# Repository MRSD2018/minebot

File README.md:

# minebot

http://mrsdprojects.ri.cmu.edu/2017teamb/

Reducing Cost, Risk, and Error in Landmine Detection

Landmines are a tragic remnant of war that the threaten economic security, mobility, and lives of people around the world. Though there has been a plethora of research in landmine sensing in the last few decades, most methods are expensive, energy-intensive, and result in a high number of false positives. ClearField Robotics aims to improve outcomes in the field by reducing the time and cost of land surveying.

By incorporating multi-modal sensing systems, we can reduce the need for singular, highly sensitive, and expensive equipment with sensor fusion. The goal of ClearField Robotics is to develop a low cost, user-friendly, and adoptable method of landmine detection without sacrificing accuracy. We combine a traditional metal detector (for broad sweeping) and an automated probing mechanism (to classify the shape of any detected metal objects) to reduce the number of false positives, increase demining speed and reduce demining costs.

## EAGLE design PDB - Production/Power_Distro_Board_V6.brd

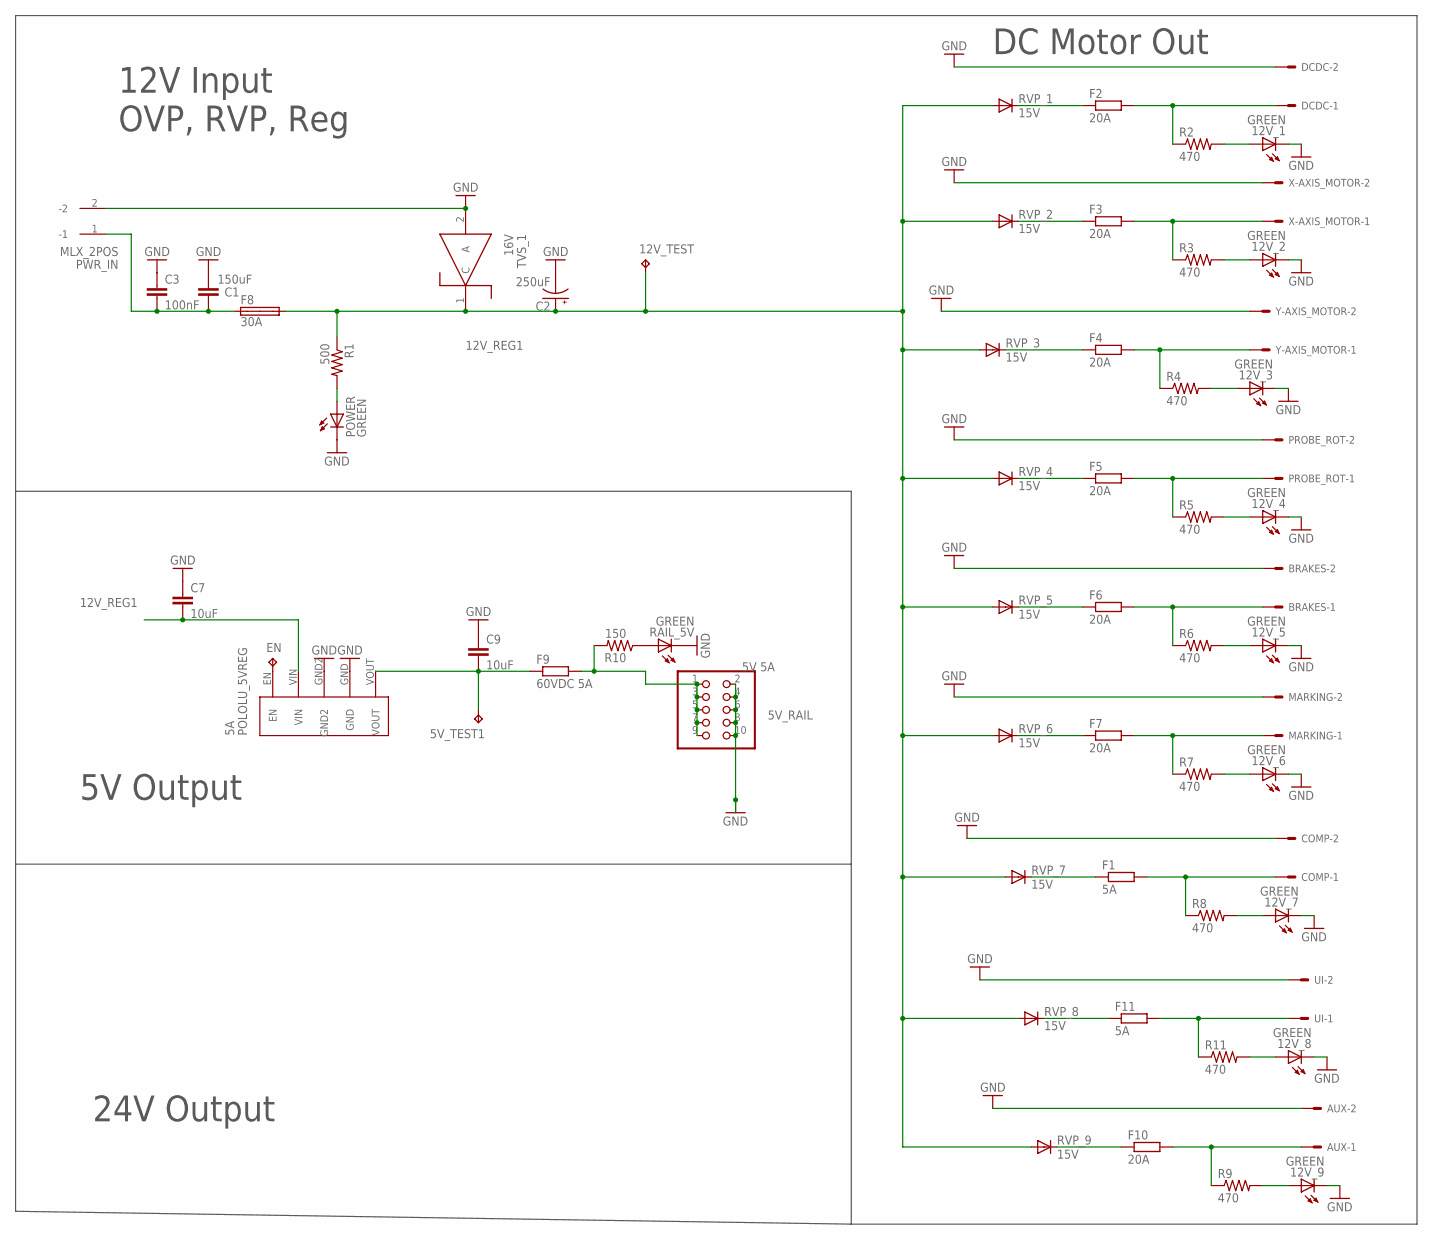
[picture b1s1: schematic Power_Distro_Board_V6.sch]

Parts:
5A: POLOLU_5VREG; SIP5
5V_RAIL: 5V 5A; 2X05
5V_TEST1, 12V_TEST: TPPAD1-13; P1-13
12V_1, 12V_2, 12V_3, 12V_4, 12V_5, 12V_6, 12V_7, 12V_8, 12V_9: GREEN; SML1206
AUX: 555X-2V; 5566-2
BRAKES: 555X-2V; 5566-2
C1: 150uF; C1210
C2: 250uF; CPOL-RADIAL-5MM-10MM
C3: 100nF; C1210
C7, C9: 10uF; C1210
COMP: 555X-2V; 5566-2
DCDC: 555X-2V; 5566-2
EN: TPPAD1-13; P1-13
F1, F11: 5A; M1206
F2, F3, F4, F5, F6, F7, F10: 20A; M1206
F8: 30A; SHK20L
F9: 60VDC 5A; M1206
MARKING: 555X-2V; 5566-2
POWER: GREEN; SML1206
PROBE_ROT: 555X-2V; 5566-2
PWR_IN: MLX_2POS; .084MLX
R1: 500; R1206
R2, R3, R4, R5, R6, R7, R8, R9, R11: 470; R1206
R10: 150; R1206
RAIL_5V: GREEN; SML1206
RVP_1, RVP_2, RVP_3, RVP_4, RVP_5, RVP_6, RVP_7, RVP_8, RVP_9: 15V; TO220ACS
TVS_1: 16V; DO-214AC
UI: 555X-2V; 5566-2
X-AXIS_MOTOR: 555X-2V; 5566-2
Y-AXIS_MOTOR: 555X-2V; 5566-2

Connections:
5V_REG3: 5V_RAIL.1, 5V_RAIL.3, 5V_RAIL.5, 5V_RAIL.7, 5V_RAIL.9, F9.2, R10.2
12V_REG1: 5A.VIN, 12V_TEST.TP, C2.+, C7.2, F8.2A, R1.1, RVP_1.A, RVP_2.A, RVP_3.A, RVP_4.A, RVP_5.A, RVP_6.A, RVP_7.A, RVP_8.A, RVP_9.A, TVS_1.1 (C)
GND: 5A.GND, 5A.GND2, 5V_RAIL.2, 5V_RAIL.4, 5V_RAIL.6, 5V_RAIL.8, 5V_RAIL.10, 12V_1.C, 12V_2.C, 12V_3.C, 12V_4.C, 12V_5.C, 12V_6.C, 12V_7.C, 12V_8.C, 12V_9.C, AUX.2, BRAKES.2, C1.2, C2.-, C3.1, C7.1, C9.1, COMP.2, DCDC.2, MARKING.2, POWER.C, PROBE_ROT.2, PWR_IN.2 (-2), RAIL_5V.C, TVS_1.2 (A), UI.2, X-AXIS_MOTOR.2, Y-AXIS_MOTOR.2
unnamed: POWER.A, R1.2
unnamed: C1.1, C3.2, F8.1A, PWR_IN.1 (-1)
unnamed: F1.1, RVP_7.C
unnamed: F2.1, RVP_1.C
unnamed: F6.1, RVP_5.C
unnamed: 5A.EN, EN.TP
unnamed: 12V_1.A, R2.2
unnamed: F10.1, RVP_9.C
unnamed: R10.1, RAIL_5V.A
unnamed: DCDC.1, F2.2, R2.1
unnamed: 12V_5.A, R6.2
unnamed: F3.1, RVP_2.C
unnamed: 12V_9.A, R9.2
unnamed: 12V_2.A, R3.2
unnamed: BRAKES.1, F6.2, R6.1
unnamed: F3.2, R3.1, X-AXIS_MOTOR.1
unnamed: F7.1, RVP_6.C
unnamed: 12V_6.A, R7.2
unnamed: F4.1, RVP_3.C
unnamed: F7.2, MARKING.1, R7.1
unnamed: 12V_3.A, R4.2
unnamed: F4.2, R4.1, Y-AXIS_MOTOR.1
unnamed: F5.1, RVP_4.C
unnamed: 12V_4.A, R5.2
unnamed: F5.2, PROBE_ROT.1, R5.1
unnamed: 12V_7.A, R8.2
unnamed: COMP.1, F1.2, R8.1
unnamed: F11.1, RVP_8.C
unnamed: 5A.VOUT, 5V_TEST1.TP, C9.2, F9.1
unnamed: 12V_8.A, R11.2
unnamed: F11.2, R11.1, UI.1
unnamed: AUX.1, F10.2, R9.1

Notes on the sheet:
12V Input OVP, RVP, Reg
DC Motor Out
5V Output
24V Output

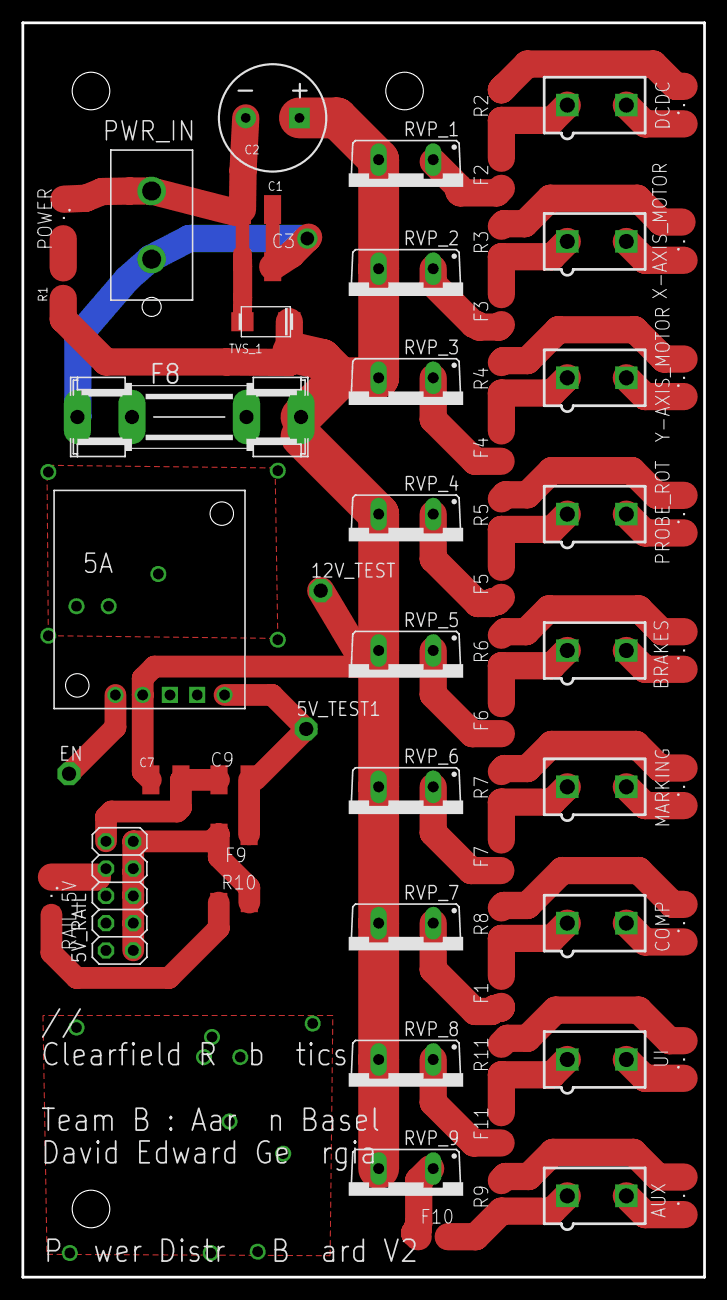
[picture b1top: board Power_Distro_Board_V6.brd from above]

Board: 2 copper layers, 63.5 x 116.8 mm, 63 parts (0 on the bottom side), 35 nets.

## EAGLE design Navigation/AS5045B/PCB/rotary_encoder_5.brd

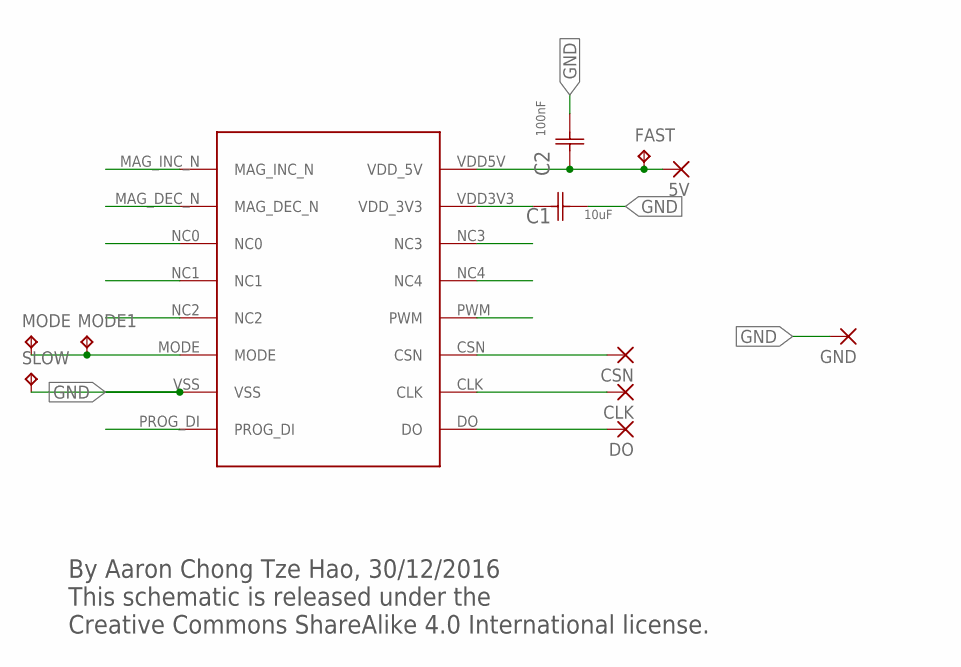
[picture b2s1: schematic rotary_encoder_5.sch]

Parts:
5V: 1,6/0,8
C1: 10uF; CAP_0805_100NF
C2: 100nF; CAP_0805_100NF
CLK: 1,6/0,8
CSN: 1,6/0,8
DO: 1,6/0,8
FAST: TPTP10SQ; TP10SQ
GND: 1,6/0,8
MODE, MODE1: TPTP10SQ; TP10SQ
SLOW: TPTP10SQ; TP10SQ
U$1: AS5045_ROTARY_ENCODER

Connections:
5V: 5V.1, C2.1 (C1), FAST.TP, U$1.VDD5V (VDD_5V)
CLK: CLK.1, U$1.CLK
CSN: CSN.1, U$1.CSN
DO: DO.1, U$1.DO
GND: C1.2 (C2), C2.2 (C2), GND.1, SLOW.TP, U$1.VSS
unnamed: MODE.TP, MODE1.TP, U$1.MODE
unnamed: C1.1 (C1), U$1.VDD3V3 (VDD_3V3)

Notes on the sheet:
By Aaron Chong Tze Hao, 30/12/2016 This schematic is released under the Creative Commons ShareAlike 4.0 International license.

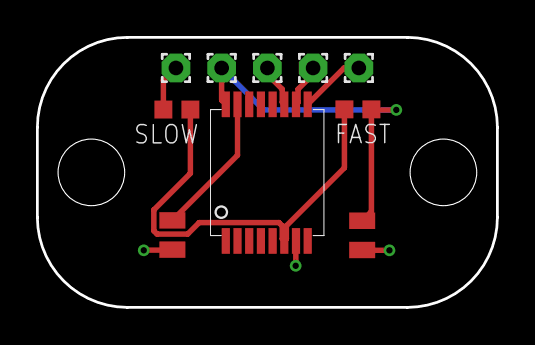
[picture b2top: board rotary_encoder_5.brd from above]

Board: 2 copper layers, 25.6 x 15.0 mm, 12 parts (0 on the bottom side), 7 nets.

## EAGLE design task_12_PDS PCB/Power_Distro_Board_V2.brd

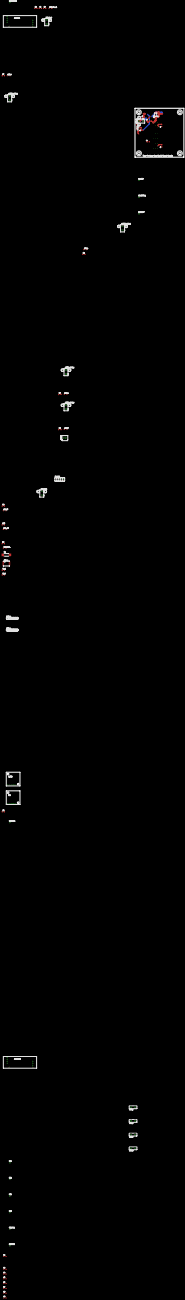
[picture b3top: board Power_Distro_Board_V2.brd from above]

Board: 2 copper layers, 63.5 x 63.6 mm, 70 parts (0 on the bottom side), 48 nets.

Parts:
2.5A, 5A: POLOLU_5VREG; SIP5
5V_RAIL: 5V 5A; 2X05
5V_TEST, 5V_TEST1, 12V_TEST, 24V_TEST_1, 24V_TEST_2: TPPAD1-13; P1-13
12V_1, 12V_2, 12V_3, 12V_4, 24V_2A_1_, 24V_2A_1_1: GREEN; SML1206
24V_2A_1, 24V_2A_2: 5566-2
24V_REG, 24V_REG1: POLOLU_24VSTEPUP; 2X4PIN_REG
C1: 150uF; C1206
C1_1: 100nF; C1206
C1_2, C3, C4, C5, C6, C7, C8, C9: 10uF; C1206
C2: 100uF; C1206
EN1, EN2: TPPAD1-13; P1-13
ENABLE1, ENABLE2: TPPAD1-13; P1-13
ENC_1: ENCODER_AS5045B; SSOP16
F1: 60VDC 50A; NANO
F2, F3, F4, F5: 60VDC 20A; R1206W
F6, F7, F8: 60VDC 3A; R1206W
F9: 60VDC 5A; R1206W
MAIN_1: 1X06
MOTOR_OUT_1, MOTOR_OUT_2, MOTOR_OUT_3, MOTOR_OUT_4: 5566-2
PG1, PG2: TPPAD1-13; P1-13
POWER: GREEN; SML1206
PWR_IN: 5566-2
R1: 500; R1206
R2, R3, R4, R7: 470; R1206
R5, R6: 1100; R1206
R9, R10: 150; R1206
RAIL_5V: GREEN; SML1206
RPI_5V: GREEN; SML1206
RPI_OUT: C-GRID-02-70543; 70543-02
RVP_1, RVP_2, RVP_3, RVP_4: 15V; TO220ACS
SUB_1: 1X06
TVS_1: 16V; DO-214AC

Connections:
5V_REG: 2.5A.VOUT, 5V_TEST.TP, C8.2, F8.1
5V_REG1: F8.2, R9.2, RPI_OUT.1
5V_REG3: 5V_RAIL.1, 5V_RAIL.3, 5V_RAIL.5, 5V_RAIL.7, 5V_RAIL.9, F9.2, R10.2
12V_REG: 12V_TEST.TP, C2.2, F1.VIN-, R1.1, RVP_1.A, RVP_2.A, RVP_3.A, RVP_4.A, TVS_1.1
12V_REG_TVS: 2.5A.VIN, 5A.VIN, 24V_REG.VIN1, 24V_REG.VIN2, 24V_REG1.VIN1, 24V_REG1.VIN2, C3.2, C5.2, C7.2
A_1: ENC_1.3, SUB_1.3
B_1: ENC_1.4, SUB_1.4
CLK_1: ENC_1.10, MAIN_1.4
CSN_1: ENC_1.11, MAIN_1.3
DO_1: ENC_1.9, MAIN_1.5
GND: 2.5A.GND, 5A.GND, 5V_RAIL.2, 5V_RAIL.4, 5V_RAIL.6, 5V_RAIL.8, 5V_RAIL.10, 12V_1.C, 12V_2.C, 12V_3.C, 12V_4.C, 24V_2A_1.2, 24V_2A_1_.C, 24V_2A_1_1.C, 24V_2A_2.2, 24V_REG.GND1, 24V_REG.GND2, 24V_REG.GND3, 24V_REG.GND4, 24V_REG1.GND1, 24V_REG1.GND2, 24V_REG1.GND3, 24V_REG1.GND4, C1.1, C2.1, C3.1, C4.1, C5.1, C6.1, C7.1, C8.1, C9.1, MOTOR_OUT_1.2, MOTOR_OUT_2.2, MOTOR_OUT_3.2, MOTOR_OUT_4.2, POWER.C, PWR_IN.2, RAIL_5V.C, RPI_5V.C, RPI_OUT.2, TVS_1.2
GND_1: C1_1.2, C1_2.2, ENC_1.7, MAIN_1.2
I_1: ENC_1.6, SUB_1.5
MAG_DEC_N_1: ENC_1.2, SUB_1.2
MAG_INC_N_1: ENC_1.1, SUB_1.1
unnamed: POWER.A, R1.2
unnamed: 2.5A.PG, PG1.TP
unnamed: C1.2, F1.VIN+, PWR_IN.1
unnamed: C1_2.1, ENC_1.15
unnamed: F2.1, RVP_1.C
unnamed: 2.5A.EN, EN1.TP
unnamed: 24V_REG1.VOUT1, 24V_REG1.VOUT2, 24V_TEST_1.TP, C4.2
unnamed: 5A.PG, PG2.TP
unnamed: 12V_1.A, R2.2
unnamed: R9.1, RPI_5V.A
unnamed: R10.1, RAIL_5V.A
unnamed: F2.2, MOTOR_OUT_1.1, R2.1
unnamed: F3.1, RVP_2.C
unnamed: 5A.EN, EN2.TP
unnamed: 12V_2.A, R3.2
unnamed: 24V_2A_1_1.A, R6.2
unnamed: F3.2, MOTOR_OUT_2.1, R3.1
unnamed: 24V_2A_1.1, F6.2, R5.1
unnamed: F4.1, RVP_3.C
unnamed: 12V_3.A, R4.2
unnamed: F4.2, MOTOR_OUT_3.1, R4.1
unnamed: F5.1, RVP_4.C
unnamed: 12V_4.A, R7.2
unnamed: F5.2, MOTOR_OUT_4.1, R7.1
unnamed: 24V_2A_1_.A, R5.2
unnamed: 24V_REG1.ENABLE, ENABLE1.TP
unnamed: 24V_REG.VOUT1, 24V_REG.VOUT2, 24V_TEST_2.TP, C6.2
unnamed: 5A.VOUT, 5V_TEST1.TP, C9.2, F9.1
unnamed: 24V_2A_2.1, F7.2, R6.1
unnamed: 24V_REG.ENABLE, ENABLE2.TP
PDIO_1: ENC_1.8, SUB_1.6
PWM_1: ENC_1.12, MAIN_1.6
VIN_1: C1_1.1, ENC_1.16, MAIN_1.1

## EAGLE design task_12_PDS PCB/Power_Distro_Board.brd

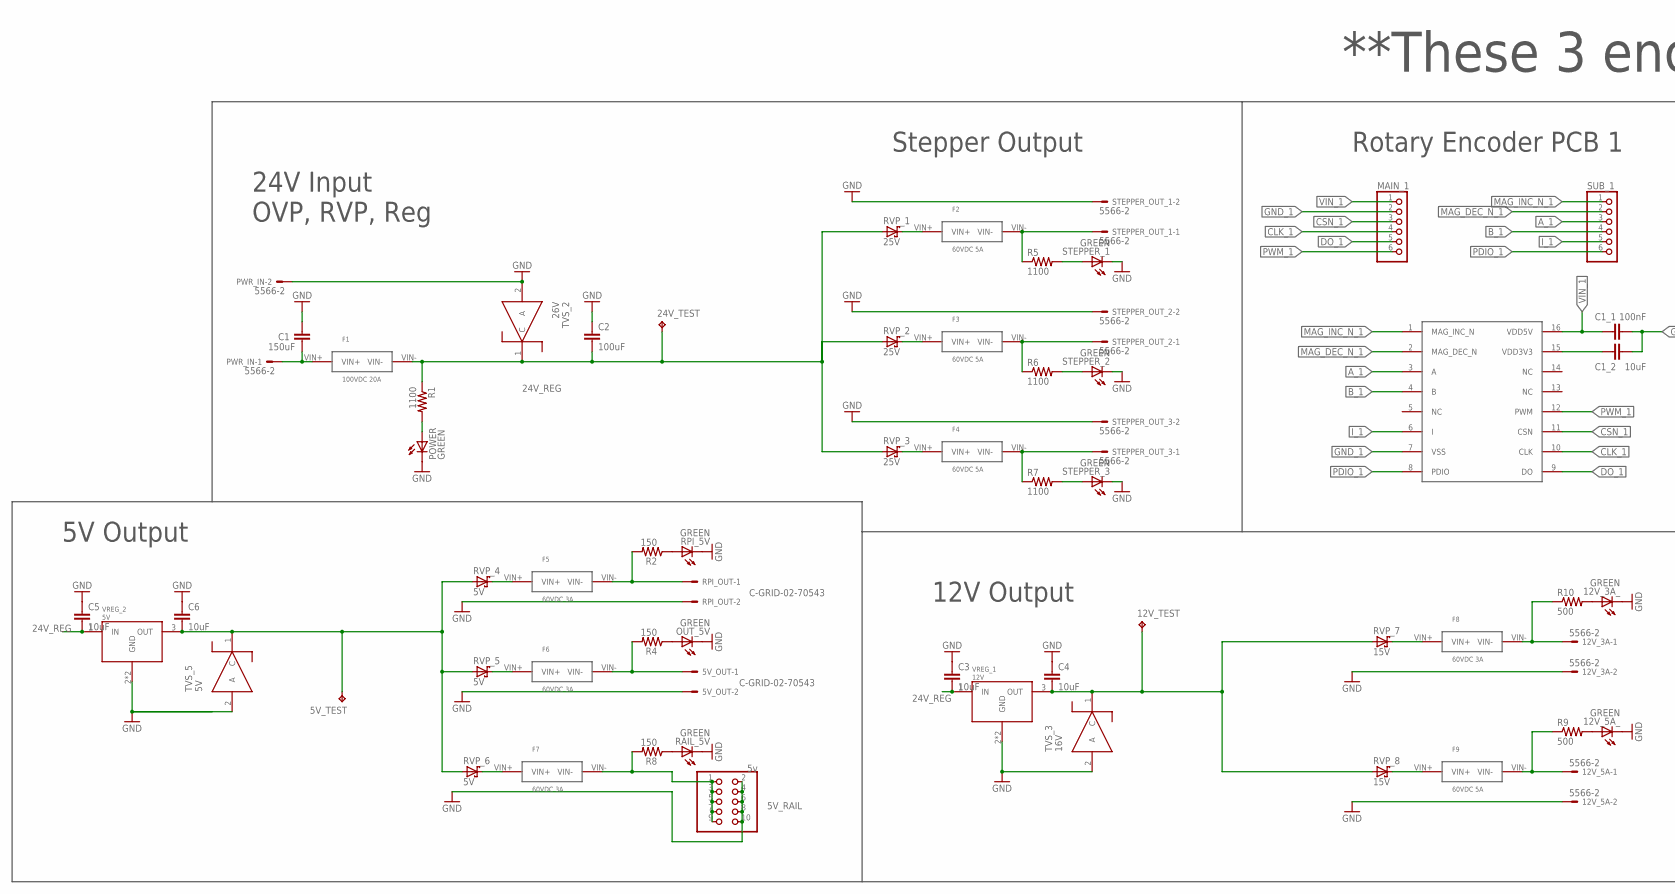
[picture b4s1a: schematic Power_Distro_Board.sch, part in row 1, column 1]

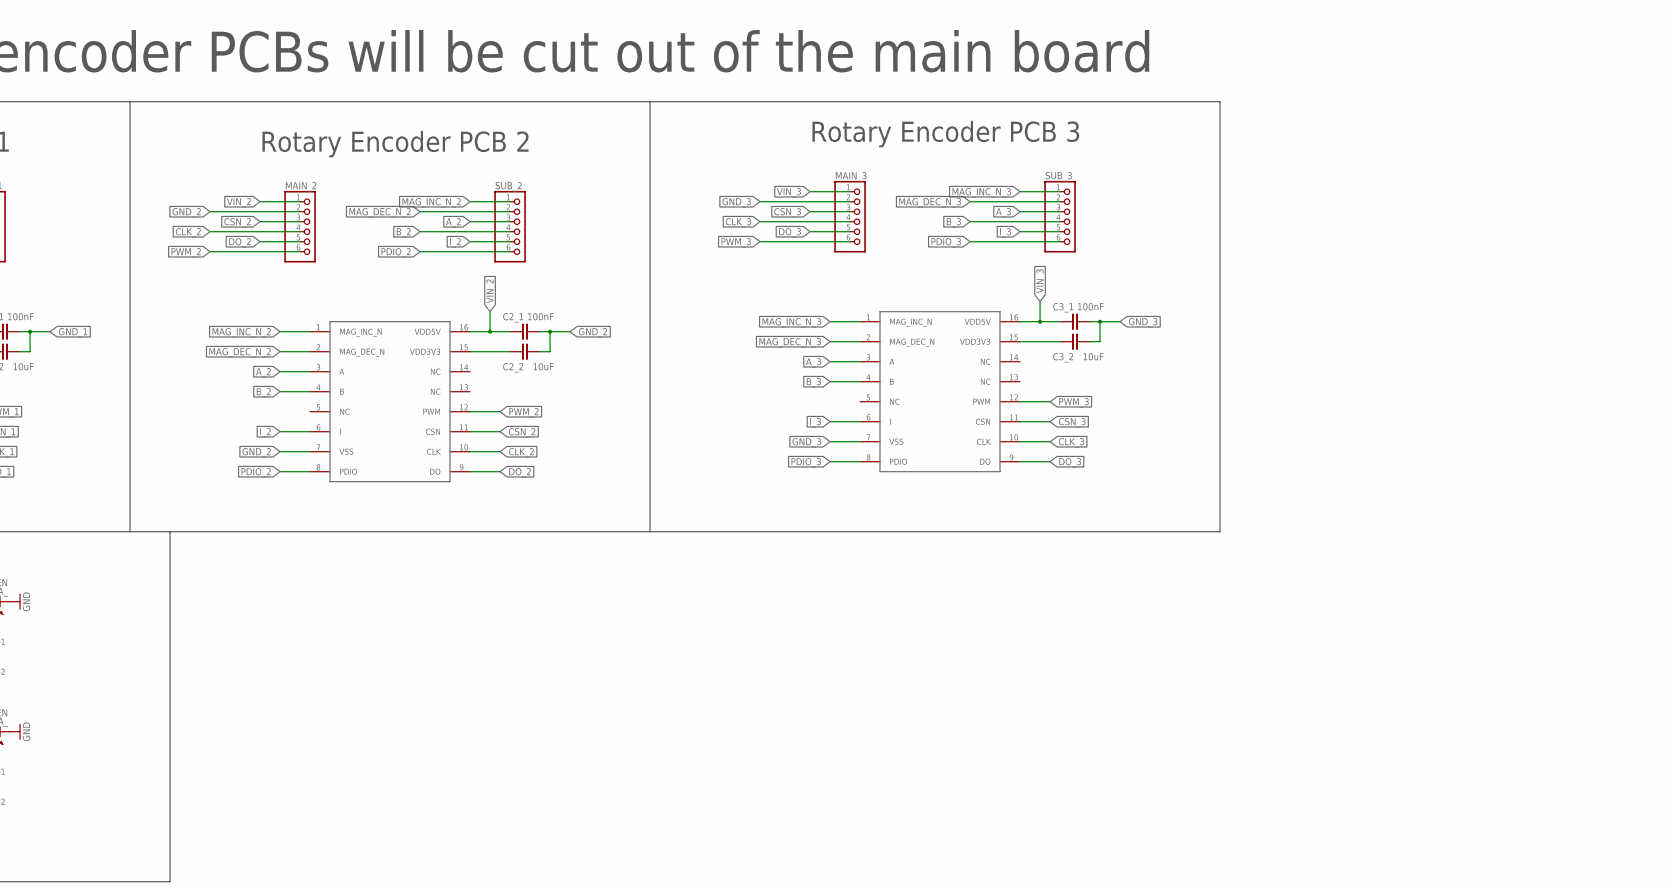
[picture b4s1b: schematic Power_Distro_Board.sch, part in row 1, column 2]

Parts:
5V_OUT: C-GRID-02-70543; 70543-02
5V_RAIL: 5v; 2X05
5V_TEST, 12V_TEST, 24V_TEST: TPPAD1-13; P1-13
12V_3A, 12V_5A: 5566-2
12V_3A_, 12V_5A_: GREEN; SML1206
C1: 150uF; C1206
C1_1, C2_1, C3_1: 100nF; C1206
C1_2, C2_2, C3, C3_2, C4, C5, C6: 10uF; C1206
C2: 100uF; C1206
ENC_1, ENC_2, ENC_3: ENCODER_AS5045B; SSOP16
F1: 100VDC 20A; NANO
F2, F3, F4, F9: 60VDC 5A; OMNI_BLOCK
F5, F6, F7, F8: 60VDC 3A; OMNI_BLOCK
MAIN_1, MAIN_2, MAIN_3: PINHD-1X6; 1X06
OUT_5V: GREEN; SML1206
POWER: GREEN; SML1206
PWR_IN: 5566-2
R1, R5, R6, R7: 1100; R1206
R2, R4, R8: 150; R1206
R9, R10: 500; R1206
RAIL_5V: GREEN; SML1206
RPI_5V: GREEN; SML1206
RPI_OUT: C-GRID-02-70543; 70543-02
RVP_1, RVP_2, RVP_3: 25V; SMC
RVP_4, RVP_5, RVP_6: 5V; SMC
RVP_7, RVP_8: 15V; SMC
STEPPER_1, STEPPER_2, STEPPER_3: GREEN; SML1206
STEPPER_OUT_1, STEPPER_OUT_2, STEPPER_OUT_3: 5566-2
SUB_1, SUB_2, SUB_3: PINHD-1X6; 1X06
TVS_2: 26V; DO-214AC
TVS_3: 16V; DO-214AC
TVS_5: 5V; DO-214AC
VREG_1: 12V; TO-263-3
VREG_2: 5V; TO-263-3

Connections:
5V_REG: 5V_TEST.TP, C6.2, RVP_4.A, RVP_5.A, RVP_6.A, TVS_5.1 (C), VREG_2.3 (OUT)
5V_REG1: F5.VIN-, R2.2, RPI_OUT.1
5V_REG2: 5V_OUT.1, F6.VIN-, R4.2
5V_REG3: 5V_RAIL.1, 5V_RAIL.3, 5V_RAIL.5, 5V_RAIL.7, 5V_RAIL.9, F7.VIN-, R8.2
12V_REG: 12V_TEST.TP, C4.2, RVP_7.A, RVP_8.A, TVS_3.1 (C), VREG_1.3 (OUT)
12V_REG1: 12V_5A.1, F9.VIN-, R9.1
12V_REG2: 12V_3A.1, F8.VIN-, R10.1
24V_REG: 24V_TEST.TP, C2.2, C3.2, C5.2, F1.VIN-, R1.1, RVP_1.A, RVP_2.A, RVP_3.A, TVS_2.1 (C), VREG_1.1 (IN), VREG_2.1 (IN)
A_1: ENC_1.3 (A), SUB_1.3
A_2: ENC_2.3 (A), SUB_2.3
A_3: ENC_3.3 (A), SUB_3.3
B_1: ENC_1.4 (B), SUB_1.4
B_2: ENC_2.4 (B), SUB_2.4
B_3: ENC_3.4 (B), SUB_3.4
CLK_1: ENC_1.10 (CLK), MAIN_1.4
CLK_2: ENC_2.10 (CLK), MAIN_2.4
CLK_3: ENC_3.10 (CLK), MAIN_3.4
CSN_1: ENC_1.11 (CSN), MAIN_1.3
CSN_2: ENC_2.11 (CSN), MAIN_2.3
CSN_3: ENC_3.11 (CSN), MAIN_3.3
DO_1: ENC_1.9 (DO), MAIN_1.5
DO_2: ENC_2.9 (DO), MAIN_2.5
DO_3: ENC_3.9 (DO), MAIN_3.5
GND: 5V_OUT.2, 5V_RAIL.2, 5V_RAIL.4, 5V_RAIL.6, 5V_RAIL.8, 5V_RAIL.10, 12V_3A.2, 12V_3A_.C, 12V_5A.2, 12V_5A_.C, C1.1, C2.1, C3.1, C4.1, C5.1, C6.1, OUT_5V.C, POWER.C, PWR_IN.2, RAIL_5V.C, RPI_5V.C, RPI_OUT.2, STEPPER_1.C, STEPPER_2.C, STEPPER_3.C, STEPPER_OUT_1.2, STEPPER_OUT_2.2, STEPPER_OUT_3.2, TVS_2.2 (A), TVS_3.2 (A), TVS_5.2 (A), VREG_1.2 (GND), VREG_1.4 (GND), VREG_2.2 (GND), VREG_2.4 (GND)
GND_1: C1_1.2, C1_2.2, ENC_1.7 (VSS), MAIN_1.2
GND_2: C2_1.2, C2_2.2, ENC_2.7 (VSS), MAIN_2.2
GND_3: C3_1.2, C3_2.2, ENC_3.7 (VSS), MAIN_3.2
I_1: ENC_1.6 (I), SUB_1.5
I_2: ENC_2.6 (I), SUB_2.5
I_3: ENC_3.6 (I), SUB_3.5
MAG_DEC_N_1: ENC_1.2 (MAG_DEC_N), SUB_1.2
MAG_DEC_N_2: ENC_2.2 (MAG_DEC_N), SUB_2.2
MAG_DEC_N_3: ENC_3.2 (MAG_DEC_N), SUB_3.2
MAG_INC_N_1: ENC_1.1 (MAG_INC_N), SUB_1.1
MAG_INC_N_2: ENC_2.1 (MAG_INC_N), SUB_2.1
MAG_INC_N_3: ENC_3.1 (MAG_INC_N), SUB_3.1
unnamed: POWER.A, R1.2
unnamed: C2_2.1, ENC_2.15 (VDD3V3)
unnamed: C1.2, F1.VIN+, PWR_IN.1
unnamed: C1_2.1, ENC_1.15 (VDD3V3)
unnamed: F2.VIN+, RVP_1.C
unnamed: C3_2.1, ENC_3.15 (VDD3V3)
unnamed: F5.VIN+, RVP_4.C
unnamed: R5.2, STEPPER_1.A
unnamed: R2.1, RPI_5V.A
unnamed: R8.1, RAIL_5V.A
unnamed: F2.VIN-, R5.1, STEPPER_OUT_1.1
unnamed: F3.VIN+, RVP_2.C
unnamed: R6.2, STEPPER_2.A
unnamed: 12V_5A_.A, R9.2
unnamed: F3.VIN-, R6.1, STEPPER_OUT_2.1
unnamed: OUT_5V.A, R4.1
unnamed: F4.VIN+, RVP_3.C
unnamed: R7.2, STEPPER_3.A
unnamed: F4.VIN-, R7.1, STEPPER_OUT_3.1
unnamed: F6.VIN+, RVP_5.C
unnamed: 12V_3A_.A, R10.2
unnamed: F7.VIN+, RVP_6.C
unnamed: F8.VIN+, RVP_7.C
unnamed: F9.VIN+, RVP_8.C
PDIO_1: ENC_1.8 (PDIO), SUB_1.6
PDIO_2: ENC_2.8 (PDIO), SUB_2.6
PDIO_3: ENC_3.8 (PDIO), SUB_3.6
PWM_1: ENC_1.12 (PWM), MAIN_1.6
PWM_2: ENC_2.12 (PWM), MAIN_2.6
PWM_3: ENC_3.12 (PWM), MAIN_3.6
VIN_1: C1_1.1, ENC_1.16 (VDD5V), MAIN_1.1
VIN_2: C2_1.1, ENC_2.16 (VDD5V), MAIN_2.1
VIN_3: C3_1.1, ENC_3.16 (VDD5V), MAIN_3.1

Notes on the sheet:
24V Input OVP, RVP, Reg
Stepper Output
5V Output
12V Output
Rotary Encoder PCB 1
Rotary Encoder PCB 2
Rotary Encoder PCB 3
**These 3 encoder PCBs will be cut out of the main board

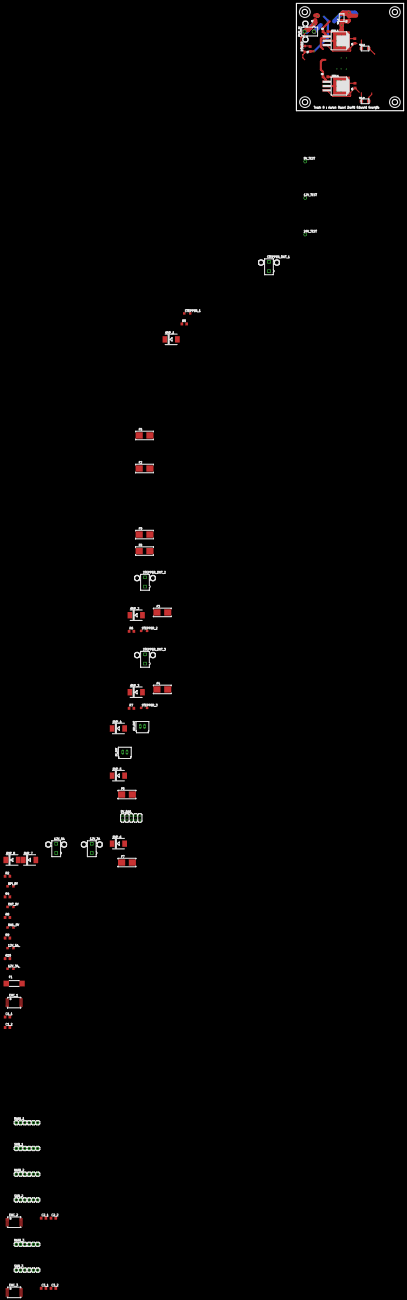
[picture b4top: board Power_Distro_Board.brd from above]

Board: 2 copper layers, 63.5 x 63.6 mm, 73 parts (0 on the bottom side), 69 nets.

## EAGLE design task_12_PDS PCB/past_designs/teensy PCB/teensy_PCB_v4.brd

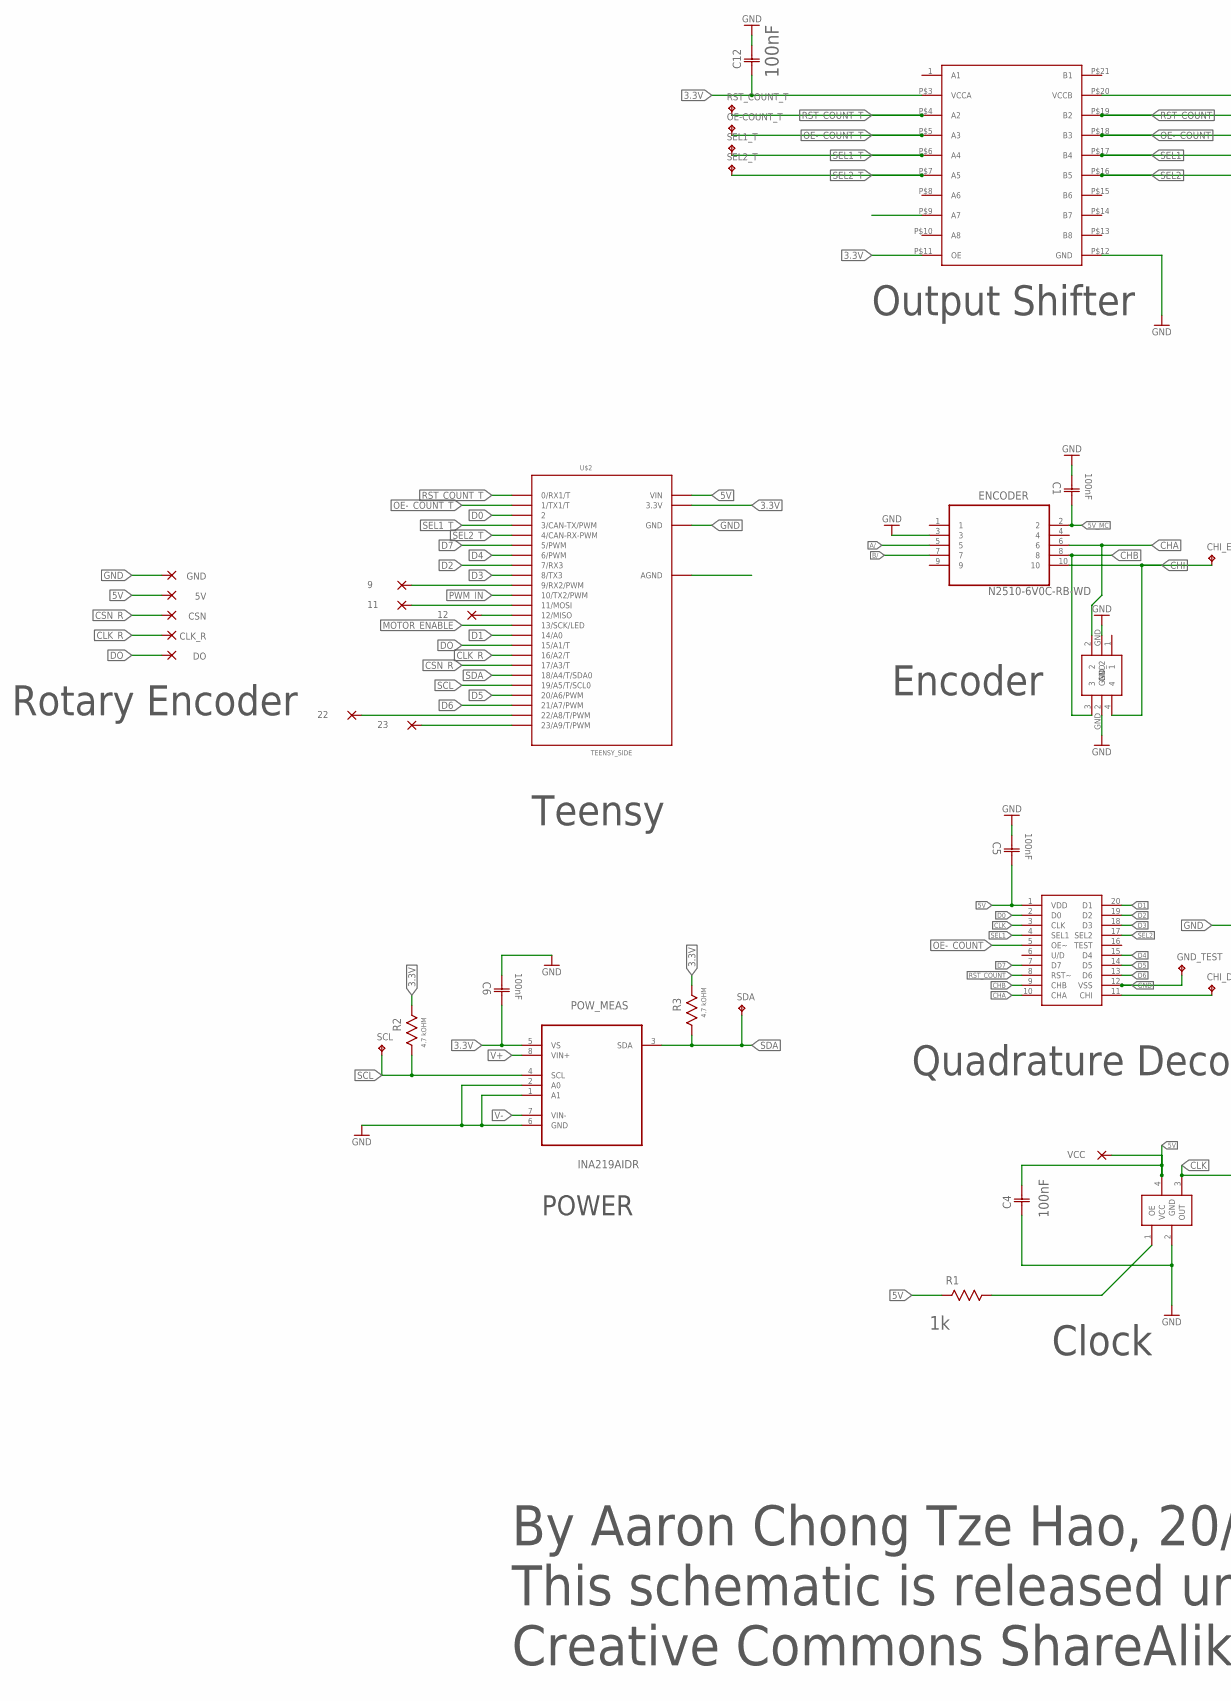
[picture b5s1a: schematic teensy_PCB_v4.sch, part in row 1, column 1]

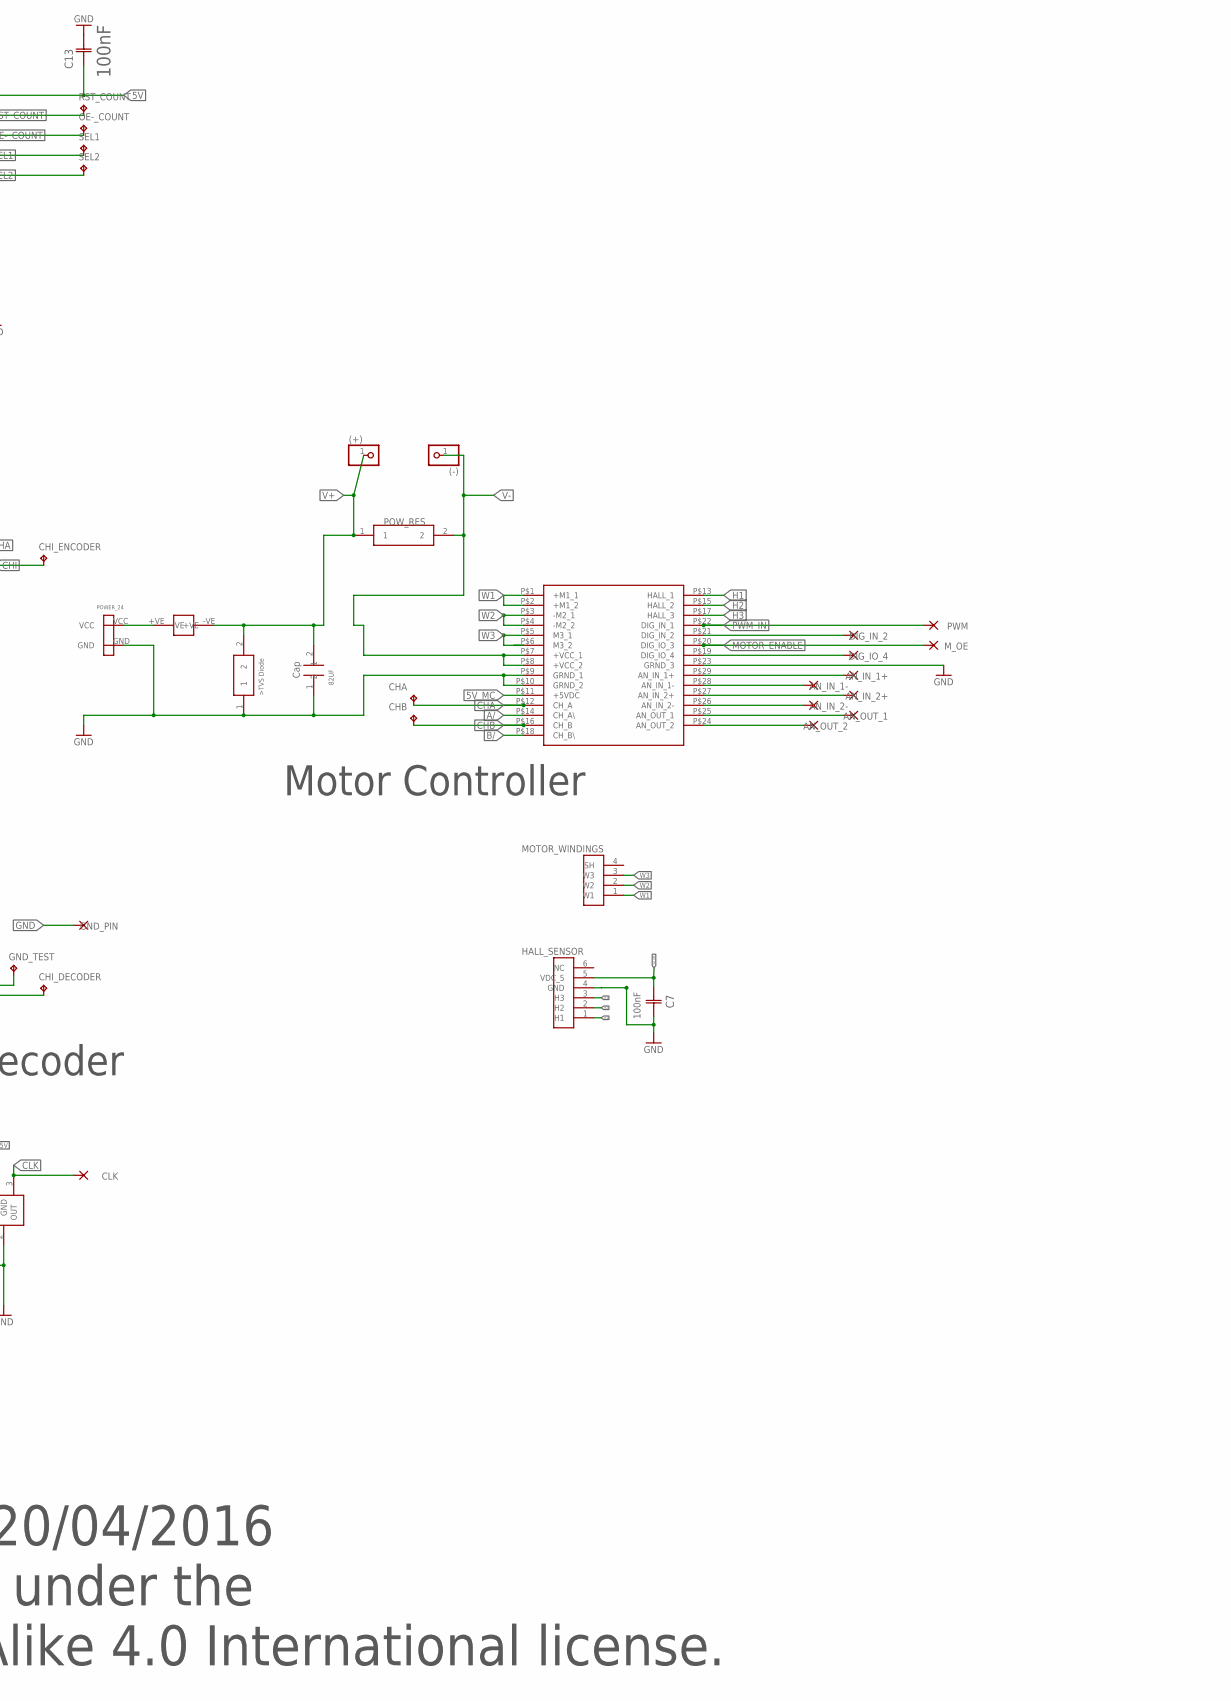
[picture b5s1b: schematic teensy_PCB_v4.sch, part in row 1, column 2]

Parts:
5V, 9, 11, 12, 22, 23: WIREPAD1,6/0,8; 1,6/0,8
(+): PINHD-1X1; 1X01
(-): PINHD-1X1; 1X01
AN_IN_1+, AN_IN_1-, AN_IN_2+, AN_IN_2-: WIREPAD1,6/0,8; 1,6/0,8
AN_OUT_1, AN_OUT_2: WIREPAD1,6/0,8; 1,6/0,8
C1, C4, C5, C6, C7: 100nF; CAPC2013X90N
C12, C13: 100nF; CAP_0805_100NF
CAP82UF: 82UF; CAP_82UF
CHA: TPTP10SQ; TP10SQ
CHB: TPTP10SQ; TP10SQ
CHI_DECODER: TPTP10SQ; TP10SQ
CHI_ENCODER: TPTP10SQ; TP10SQ
CLK: WIREPAD1,6/0,8; 1,6/0,8
CLK_R: WIREPAD1,6/0,8; 1,6/0,8
CLOCK: CLOCK_14MHZ
CSN: WIREPAD1,6/0,8; 1,6/0,8
DIG_IN_2: WIREPAD1,6/0,8; 1,6/0,8
DIG_IO_4: WIREPAD1,6/0,8; 1,6/0,8
DO: WIREPAD1,6/0,8; 1,6/0,8
ENCODER: N2510-6V0C-RB-WD; 3M_N2510-6V0C-RB-WD
ENCODER_DIODE: ENCODER_DIODE_ESDA14V2BP6
FUSE_HOLDER: FUSE_HOLDER
GND: WIREPAD1,6/0,8; 1,6/0,8
GND_PIN: WIREPAD1,6/0,8; 1,6/0,8
GND_TEST: TPTP10SQ; TP10SQ
HALL_SENSOR: HALL_SENSOR_SOCKET_6POS
MOTOR_CONTROLLER: MAXON_438725THROUGH_HOLE; MAXON_MOTOR_CONTROLLER
MOTOR_WINDINGS: MOTOR_HEADER_4POS
M_OE: WIREPAD1,6/0,8; 1,6/0,8
OE-COUNT_T: TPTP10SQ; TP10SQ
OE-_COUNT: TPTP10SQ; TP10SQ
POWER_RESISTOR: POWER_RESISTOR
POW_MEAS: INA219AIDR; SOIC127P600X175-8N
PWM: WIREPAD1,6/0,8; 1,6/0,8
QUADRATURE_DECODER: HCTL-2022
R1: 1k; RESC1608X60N
R2, R3: 4.7 kOHM; RESC2013X65N
RST_COUNT: TPTP10SQ; TP10SQ
RST_COUNT_T: TPTP10SQ; TP10SQ
SCL: TPTP10SQ; TP10SQ
SDA: TPTP10SQ; TP10SQ
SEL1, SEL1_T, SEL2, SEL2_T: TPTP10SQ; TP10SQ
TVS_DIODE: TVS_SMBJ33A-E3/52
U$2: TEENSY_SIDE
U$3: TXS0108PWR
U$5: POWER_2POS
VCC: WIREPAD1,6/0,8; 1,6/0,8

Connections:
3.3V: C6.2 (C2), C12.1 (C1), POW_MEAS.5 (VS), R2.1 (R1), R3.1 (R1), U$2.3.3V, U$3.P$3 (VCCA), U$3.P$11 (OE)
5V: 5V.1, C4.2 (C2), C5.2 (C2), C13.1 (C1), CLOCK.4 (VCC), QUADRATURE_DECODER.1 (VDD), R1.2 (R2), U$2.VIN, U$3.P$20 (VCCB), VCC.1
5V_MC: C1.2 (C2), C7.2 (C2), ENCODER.2, HALL_SENSOR.5 (VDC_5), MOTOR_CONTROLLER.P$11 (+5VDC)
A/: ENCODER.5, MOTOR_CONTROLLER.P$14 (CH_A\\)
B/: ENCODER.7, MOTOR_CONTROLLER.P$18 (CH_B\\)
CHA: CHA.TP, ENCODER.6, ENCODER_DIODE.2, MOTOR_CONTROLLER.P$12 (CH_A), QUADRATURE_DECODER.10 (CHA)
CHB: CHB.TP, ENCODER.8, ENCODER_DIODE.3, MOTOR_CONTROLLER.P$16 (CH_B), QUADRATURE_DECODER.9 (CHB)
CHI: CHI_ENCODER.TP, ENCODER.10, ENCODER_DIODE.4
CLK: CLK.1, CLOCK.3 (OUT), QUADRATURE_DECODER.3 (CLK)
CLK_R: CLK_R.1, U$2.16/A2 (16/A2/T)
CSN_R: CSN.1, U$2.17/A3 (17/A3/T)
D0: QUADRATURE_DECODER.2 (D0), U$2.2
D1: QUADRATURE_DECODER.20 (D1), U$2.14/A0
D2: QUADRATURE_DECODER.19 (D2), U$2.7 (7/RX3)
D3: QUADRATURE_DECODER.18 (D3), U$2.8 (8/TX3)
D4: QUADRATURE_DECODER.15 (D4), U$2.6 (6/PWM)
D5: QUADRATURE_DECODER.14 (D5), U$2.20/A6 (20/A6/PWM)
D6: QUADRATURE_DECODER.13 (D6), U$2.21/A7 (21/A7/PWM)
D7: QUADRATURE_DECODER.7 (D7), U$2.5 (5/PWM)
DO: DO.1, U$2.15/A1 (15/A1/T)
GND: C1.1 (C1), C4.1 (C1), C5.1 (C1), C6.1 (C1), C7.1 (C1), C12.2 (C2), C13.2 (C2), CAP82UF.1, CLOCK.2 (GND), ENCODER.3, ENCODER_DIODE.GND, ENCODER_DIODE.GND_2, GND.1, GND_PIN.1, GND_TEST.TP, HALL_SENSOR.4 (GND), MOTOR_CONTROLLER.P$9 (GRND_1), MOTOR_CONTROLLER.P$10 (GRND_2), MOTOR_CONTROLLER.P$23 (GRND_3), POW_MEAS.1 (A1), POW_MEAS.2 (A0), POW_MEAS.6 (GND), QUADRATURE_DECODER.12 (VSS), TVS_DIODE.1, U$2.GND, U$3.P$12 (GND), U$5.GND
H1: HALL_SENSOR.1 (H1), MOTOR_CONTROLLER.P$13 (HALL_1)
H2: HALL_SENSOR.2 (H2), MOTOR_CONTROLLER.P$15 (HALL_2)
H3: HALL_SENSOR.3 (H3), MOTOR_CONTROLLER.P$17 (HALL_3)
MOTOR_ENABLE: MOTOR_CONTROLLER.P$20 (DIG_IO_3), M_OE.1, U$2.13 (13/SCK/LED)
MOTOR_ENABLE_T: U$3.P$9 (A7)
unnamed: FUSE_HOLDER.+VE, U$5.VCC
unnamed: DIG_IN_2.1, MOTOR_CONTROLLER.P$21 (DIG_IN_2)
unnamed: DIG_IO_4.1, MOTOR_CONTROLLER.P$19 (DIG_IO_4)
unnamed: CLOCK.1 (OE), R1.1 (R1)
unnamed: AN_IN_1+.1, MOTOR_CONTROLLER.P$29 (AN_IN_1+)
unnamed: AN_IN_1-.1, MOTOR_CONTROLLER.P$28 (AN_IN_1-)
unnamed: AN_IN_2+.1, MOTOR_CONTROLLER.P$27 (AN_IN_2+)
unnamed: AN_IN_2-.1, MOTOR_CONTROLLER.P$26 (AN_IN_2-)
unnamed: CHI_DECODER.TP, QUADRATURE_DECODER.11 (CHI)
unnamed: AN_OUT_1.1, MOTOR_CONTROLLER.P$25 (AN_OUT_1)
unnamed: AN_OUT_2.1, MOTOR_CONTROLLER.P$24 (AN_OUT_2)
unnamed: 11.1, U$2.11 (11/MOSI)
unnamed: 12.1, U$2.12 (12/MISO)
unnamed: 9.1, U$2.9 (9/RX2/PWM)
unnamed: 22.1, U$2.22/A8 (22/A8/T/PWM)
unnamed: 23.1, U$2.23/A9 (23/A9/T/PWM)
OE-_COUNT: OE-_COUNT.TP, QUADRATURE_DECODER.5 (OE~), U$3.P$18 (B3)
OE-_COUNT_T: OE-COUNT_T.TP, U$2.1 (1/TX1/T), U$3.P$5 (A3)
PWM_IN: MOTOR_CONTROLLER.P$22 (DIG_IN_1), PWM.1, U$2.10 (10/TX2/PWM)
RST_COUNT: QUADRATURE_DECODER.8 (RST~), RST_COUNT.TP, U$3.P$19 (B2)
RST_COUNT_T: RST_COUNT_T.TP, U$2.0 (0/RX1/T), U$3.P$4 (A2)
SCL: POW_MEAS.4 (SCL), R2.2 (R2), SCL.TP, U$2.19/A5 (19/A5/T/SCL0)
SDA: POW_MEAS.3 (SDA), R3.2 (R2), SDA.TP, U$2.18/A4 (18/A4/T/SDA0)
SEL1: QUADRATURE_DECODER.4 (SEL1), SEL1.TP, U$3.P$17 (B4)
SEL1_T: SEL1_T.TP, U$2.3 (3/CAN-TX/PWM), U$3.P$6 (A4)
SEL2: QUADRATURE_DECODER.17 (SEL2), SEL2.TP, U$3.P$16 (B5)
SEL2_T: SEL2_T.TP, U$2.4 (4/CAN-RX-PWM), U$3.P$7 (A5)
V+: (+).1, CAP82UF.2, FUSE_HOLDER.-VE, POWER_RESISTOR.1, POW_MEAS.8 (VIN+), TVS_DIODE.2
V-: (-).1, MOTOR_CONTROLLER.P$7 (+VCC_1), MOTOR_CONTROLLER.P$8 (+VCC_2), POWER_RESISTOR.2, POW_MEAS.7 (VIN-)
W1: MOTOR_CONTROLLER.P$1 (+M1_1), MOTOR_CONTROLLER.P$2 (+M1_2), MOTOR_WINDINGS.1 (W1)
W2: MOTOR_CONTROLLER.P$3 (-M2_1), MOTOR_CONTROLLER.P$4 (-M2_2), MOTOR_WINDINGS.2 (W2)
W3: MOTOR_CONTROLLER.P$5 (M3_1), MOTOR_CONTROLLER.P$6 (M3_2), MOTOR_WINDINGS.3 (W3)

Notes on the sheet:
Encoder
Motor Controller
Clock
POWER
Quadrature Decoder
Rotary Encoder
Teensy
Output Shifter
By Aaron Chong Tze Hao, 20/04/2016 This schematic is released under the Creative Commons ShareAlike 4.0 International license.

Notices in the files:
parts and their libraries:
SparkFun-Capacitors: Licensing: Creative Commons ShareAlike 4.0 International - https://creativecommons.org/licenses/by-sa/4.0
